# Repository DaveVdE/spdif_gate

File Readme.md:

# SPDIF Gate

Forked from [Elehobica's wonderful work](https://github.com/elehobica/pico_spdif_rx) on decoding the S/PDIF protocol on the RP2040's
PIO state machine, I used it to make this small program. I did however break the fork link so that I would not create a PR on the
upstream repo by mistake.

All credit is due to Elehobica's work. Most of the files in this repository come from upstream, I simply added the "spdif_gate" application
in the samples folder.

This project started to solve a problem that was created by "Smart TVs" that don't go to sleep when you think they do. They keep humming 
in the background when the display is off, keeping a steady bit stream on their TOSLINK outputs. A family member uses a hairing aid and has 
the problem that a device he uses to convert the TV's optical audio into a bluetooth audio stream doesn't fully turn off when the TV is not 
in use, causing continuous audio cues as he moves around the house upon his hearing aid establishing link with the device near the TV.

I built a device with a custom PCB around a Raspberry Pi Pico, fitted with an optical receiver and transmitter with an AND gate in between 
(technically a quad NAND of which to gates are configured as an AND gate) so that the RP2040 can read the incoming S/PDIF signal and 
decide if real audio is transmitted or if it's just an empty stream with no audio, and turn the gate on and off accordingly 
(with a preset timeout of 3 minutes).

You can find some photos in the photos directory, the schematics and PCB files in the board directory and CAD models for the enclosure in the models directory.

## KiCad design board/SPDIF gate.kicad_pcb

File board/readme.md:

This folder contains the schematic and PCB files from KiCad

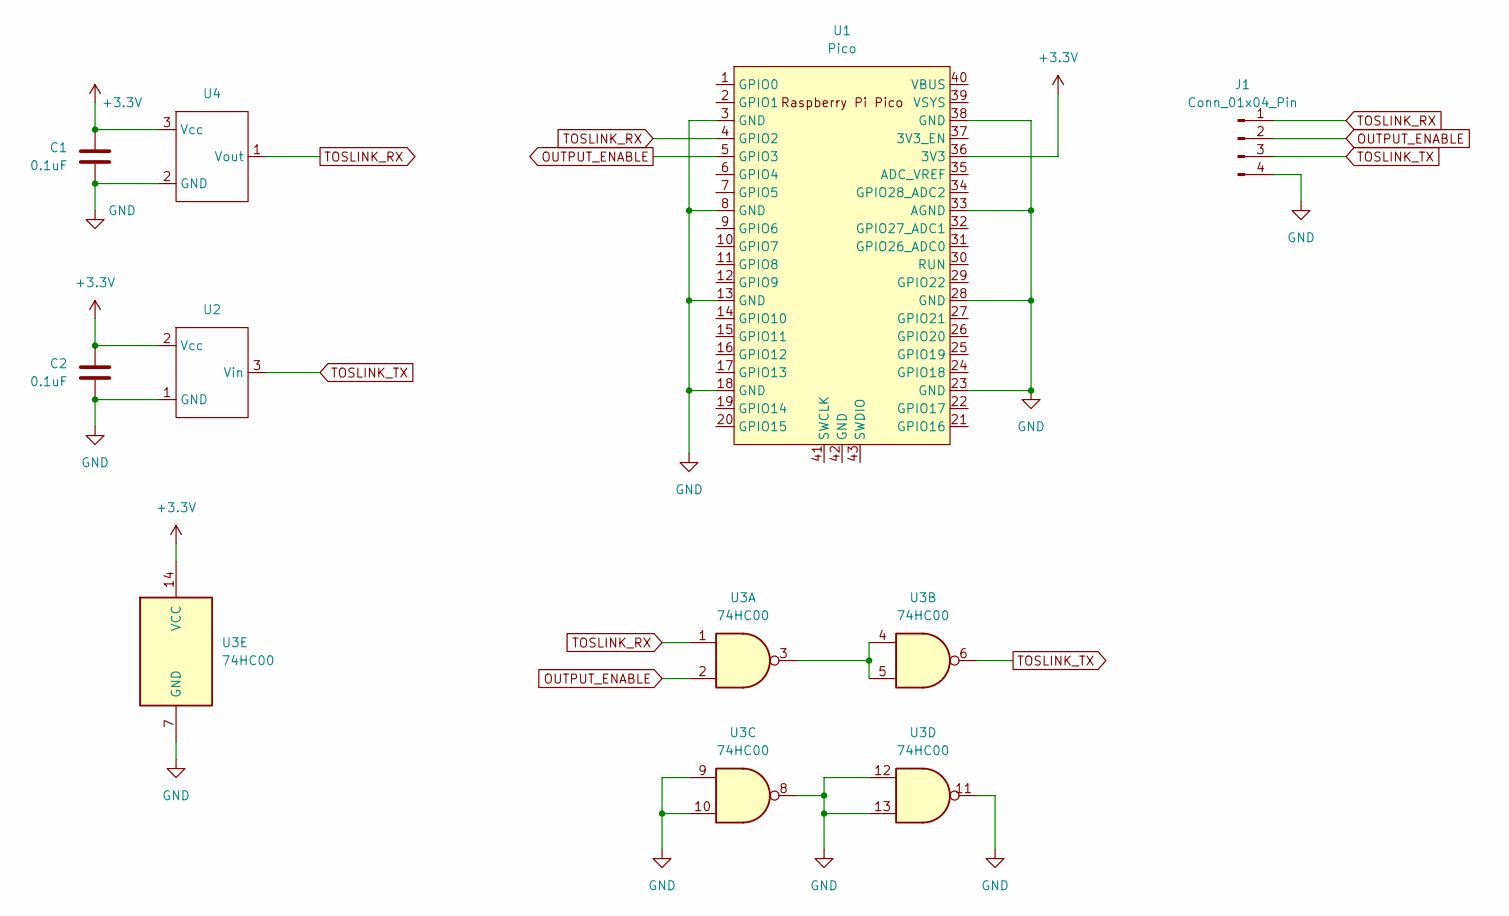
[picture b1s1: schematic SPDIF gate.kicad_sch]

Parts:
C1, C2: 0.1uF; C_0805_2012Metric
J1: Conn_01x04_Pin; PinHeader_1x04_P2.54mm_Vertical
U1: Pico; RPi_Pico_SMD_TH
U2: OTJ-1
U3: 74HC00; SOIC-14_3.9x8.7mm_P1.27mm
U4: ORJ-1

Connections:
+3.3V: C1.1, C2.1, U1.36 (3V3), U2.2 (Vcc), U3.14 (VCC), U4.3 (Vcc)
GND: C1.2, C2.2, J1.4, U1.3 (GND), U1.8 (GND), U1.13 (GND), U1.18 (GND), U1.23 (GND), U1.28 (GND), U1.33 (AGND), U1.38 (GND), U2.1 (GND), U3.7 (GND), U3.8, U3.9, U3.10, U3.11, U3.12, U3.13, U4.2 (GND)
unnamed: U3.3, U3.4, U3.5
OUTPUT_ENABLE: J1.2, U1.5 (GPIO3), U3.2
TOSLINK_RX: J1.1, U1.4 (GPIO2), U3.1, U4.1 (Vout)
TOSLINK_TX: J1.3, U2.3 (Vin), U3.6

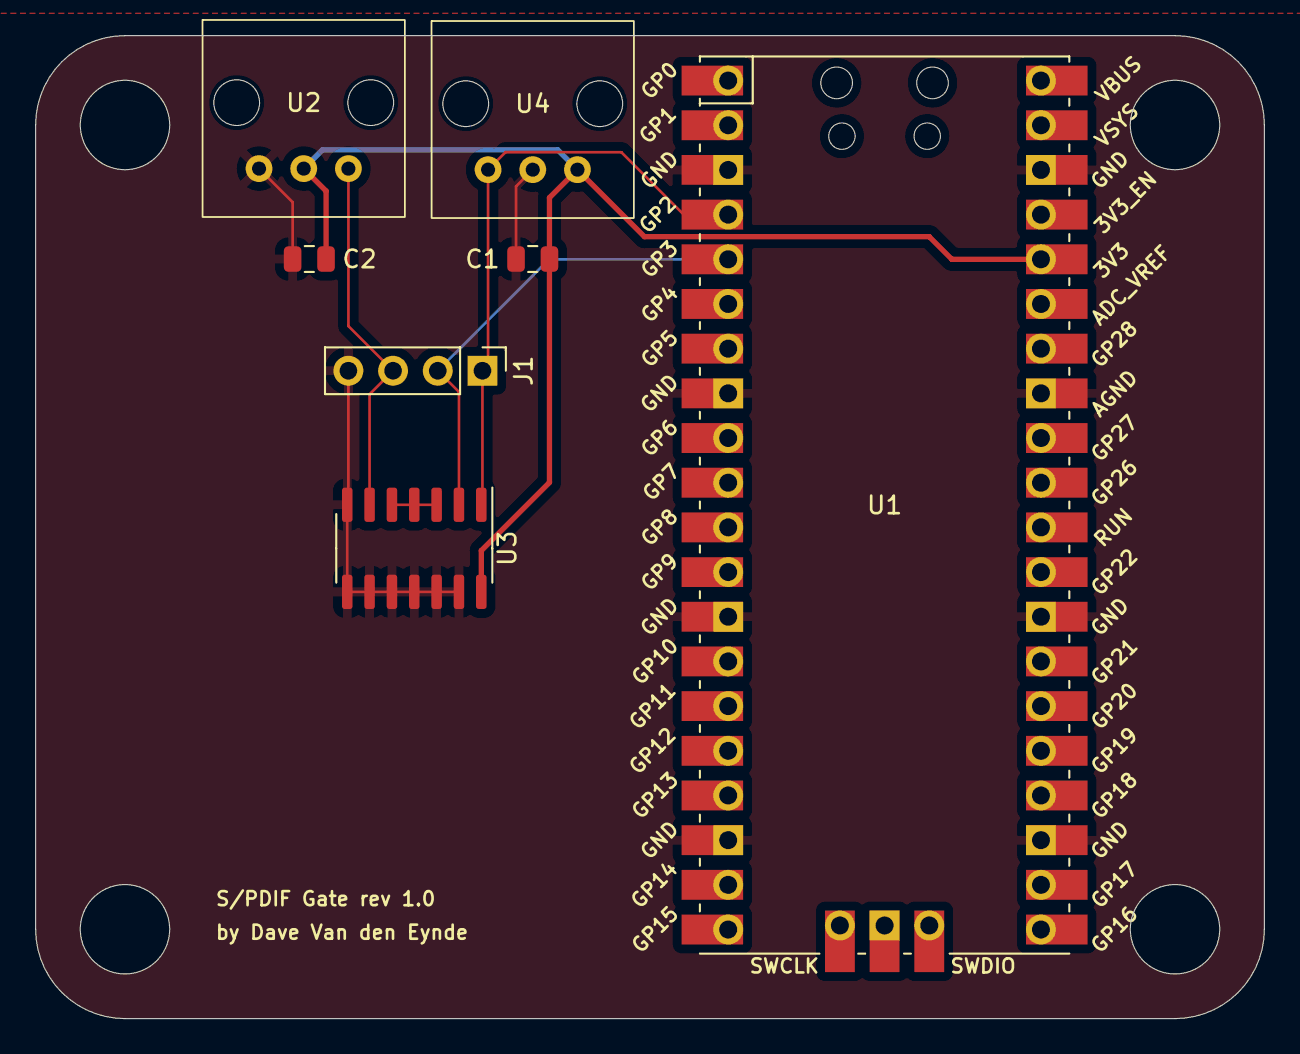
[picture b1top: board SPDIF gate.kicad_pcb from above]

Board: 2 copper layers, 69.8 x 55.9 mm, 7 parts (0 on the bottom side), 6 nets.

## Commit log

2024-01-30 Added implementation of spdif gate.
2024-01-31 Add files via upload
    Adding CAD models as well as printables.
2024-01-31 Adding some photos.
